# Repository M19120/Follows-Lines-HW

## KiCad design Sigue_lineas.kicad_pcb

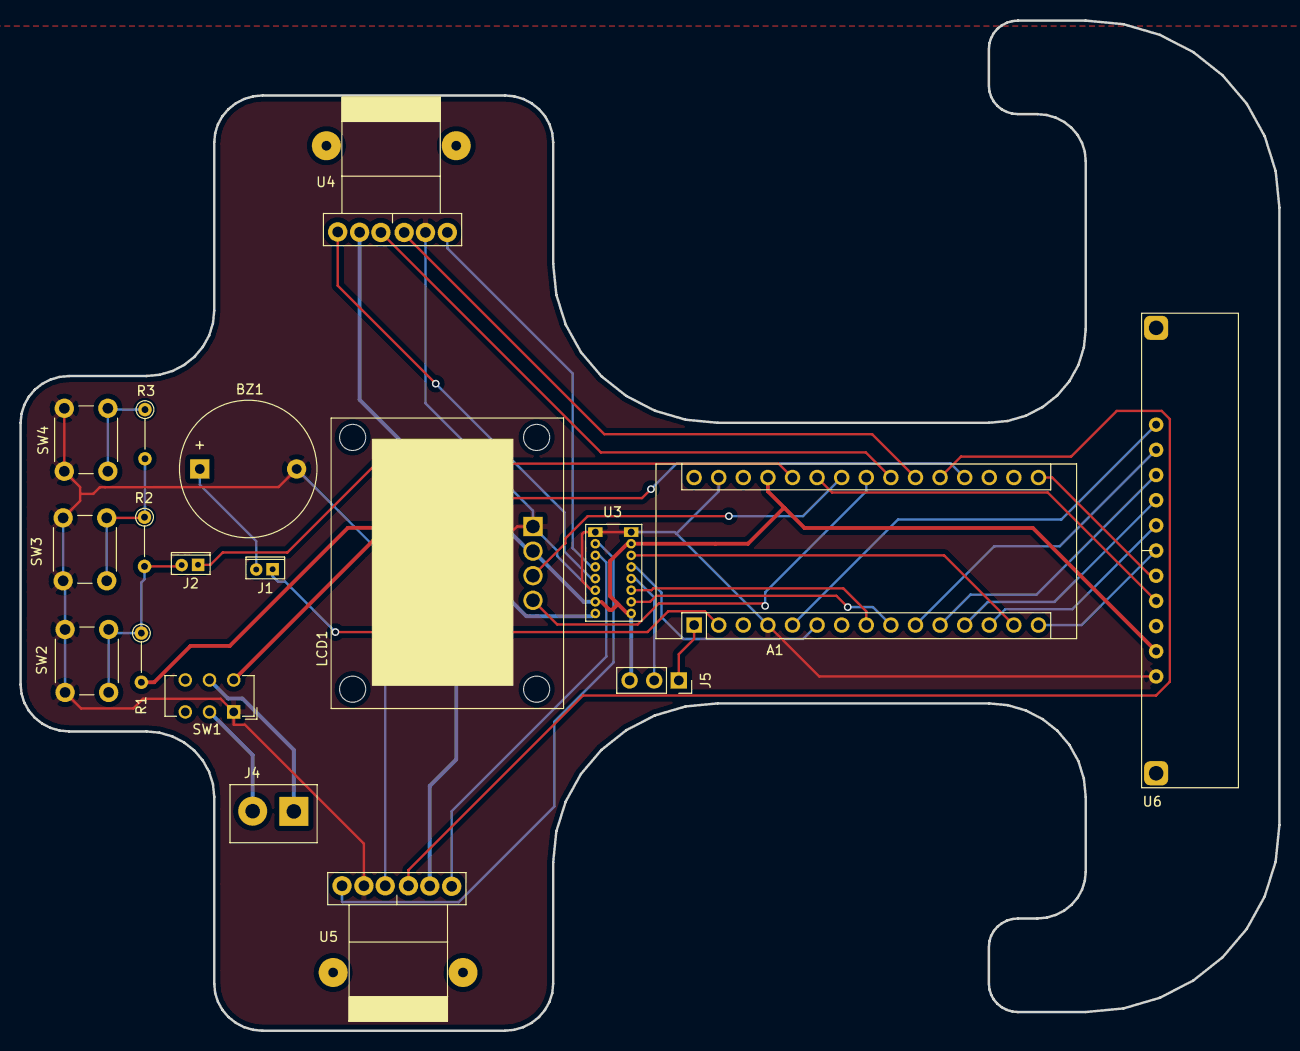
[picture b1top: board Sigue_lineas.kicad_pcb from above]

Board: 2 copper layers, 130.0 x 104.3 mm, 19 parts (1 on the bottom side), 35 nets.

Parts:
A1: Arduino_Nano_v2.x; Arduino_Nano
BZ1: Buzzer; Buzzer_D14mm_H7mm_P10mm
J1: BUTTON; Button_selector
J2: BUTTON_SELECTION; Button_selector
J4: BATT_12V; BATT12-V
J5: Conn_01x03_Female; PinSocket_1x03_P2.54mm_Vertical
LCD1: OLED-SSD1306-12C; OLED-SSD-1306-I2C
R1: 2k; R_Axial_DIN0204_L3.6mm_D1.6mm_P5.08mm_Vertical
R2, R3: 1k; R_Axial_DIN0204_L3.6mm_D1.6mm_P5.08mm_Vertical
SW1: SW_DPDT_x2; SW_CuK_JS202011CQN_DPDT_Straight
SW2, SW3, SW4: SW_Push; SW_PUSH_6mm_H5mm
U2: MP1584
U3: TB6612FBG; TB6612FNG
U4, U5: N20-encoder; n20_motor_encoder
U6: QTR-8RC

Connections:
+5V: A1.27, J5.3, LCD1.2, R1.2, U2.3, U3.15, U3.20, U3.23, U4.2, U5.2, U6.18
+12V: SW1.4, U2.2, U3.24
+BATT: J4.2, SW1.5
-BATT: J4.1, SW1.2
BUTTON: A1.26, J2.1
GND: A1.4, A1.29, BZ1.2, LCD1.1, SW1.1, SW2.2, SW3.2, SW4.2, U2.1, U2.4, U3.3, U3.9, U3.18, U4.5, U5.5, U6.19
M1-ENCDR-A: A1.22, U4.3
M1-ENCDR-B: A1.21, U4.4
M2-ENCDR-A: A1.20, U5.3
M2-ENCDR-B: A1.19, U5.4
MOTOR-1A: A1.8, U3.21
MOTOR-1B: A1.9, U3.22
MOTOR-2A: A1.6, U3.17
MOTOR-2B: A1.14, U3.16
MOTOR-EN: J5.2, U3.19
unnamed: BZ1.1, J1.2
unnamed: J2.2, R1.1, R2.2, SW2.1
unnamed: R2.1, R3.2, SW3.1
unnamed: R3.1, SW4.1
unnamed: U3.1, U4.1
unnamed: U3.5, U4.6
unnamed: U3.7, U5.6
unnamed: U3.11, U5.1
OLED-SCL: A1.24, LCD1.3
OLED-SDA: A1.23, LCD1.4
QTR-1: A1.5, U6.1
QTR-2: A1.10, U6.2
QTR-3: A1.11, U6.3
QTR-4: A1.12, U6.4
QTR-5: A1.13, U6.5
QTR-6: A1.15, U6.6
QTR-7: A1.16, U6.7
QTR-8: A1.25, U6.8
SERIAL-RX: A1.2, J1.1
SERIAL-TX: A1.1, J5.1

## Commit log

2024-09-28 README.md
